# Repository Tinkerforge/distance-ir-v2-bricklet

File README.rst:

Distance IR Bricklet 2.0
========================

This repository contains the firmware source code and the hardware design
files. The documentation generator configs can be found at
https://github.com/Tinkerforge/generators

Repository Content
------------------

software/:
 * examples/: Examples for all supported languages
 * build/: Compiled files
 * src/: Source code of firmware
 * Makefile: Makefile to build project

hardware/:
 * Contains KiCad project files and additionally schematics as PDF

datasheets/:
 * Contains datasheets for sensors and complex ICs that are used

Hardware
--------

The hardware is designed with the open source EDA Suite KiCad
(http://www.kicad.org). Before you are able to open the files,
you have to install the Tinkerforge kicad-libraries
(https://github.com/Tinkerforge/kicad-libraries). You can either clone
them directly in hardware/ or clone them in a separate folder and
symlink them into hardware/
(ln -s kicad_path/kicad-libraries project_path/hardware). After that you
can open the .pro file in hardware/ with KiCad and from there view and
modify the schematics and the PCB layout.

Software
--------

If you want to do your own Brick/Bricklet firmware development we highly
recommend that you use our build environment setup script and read the
tutorial (https://www.tinkerforge.com/en/doc/Tutorials/Tutorial_Build_Environment/Tutorial.html).

To compile the C code we recommend you to install the newest GNU Arm Embedded
Toolchain (https://launchpad.net/gcc-arm-embedded/+download).
You also need to install bricklib2 (https://github.com/Tinkerforge/bricklib2).

You can either clone it directly in software/src/ or clone it in a
separate folder and symlink it into software/src/
(ln -s bricklib_path/bricklib2 project_path/software/src/). Finally make sure to
have CMake installed (http://www.cmake.org/cmake/resources/software.html).

After that you can build the firmware by invoking make in software/.
The firmware (.zbin) can then be found in software/build/ and uploaded
with brickv (click button "Flashing" on start screen).

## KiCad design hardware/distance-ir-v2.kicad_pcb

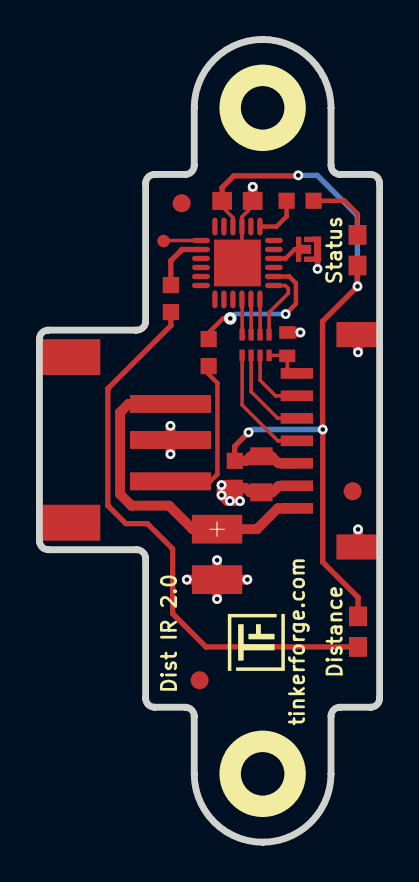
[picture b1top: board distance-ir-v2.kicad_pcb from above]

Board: 2 copper layers, 18.9 x 44.6 mm, 24 parts (2 on the bottom side), 19 nets.

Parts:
C1: 100nF; C0603E
C2: 100µF/10V; 3528-21
C3: 220pF; C0402E
C4: 10uF; C0805
C5: 1uF; C0603F
D1: blue; D0603E
D2: green; D0603E
Fiducial_Mark: VAL**; Fiducial_Mark
Fiducial_Mark#2, Fiducial_Mark#3: VAL**; Fiducial_Mark
P1: CON-SENSOR2
P2: DEBUG; DEBUG_PAD
P3: BOOT; SolderJumper
P4: S3B-PH-SM4
R2, R3, R4: 1k; R0603F
RP1: 82; 4X0402
Ref**: Val**; Logo_31x31
U2, U3: DRILL; DRILL_NP
U4: XMC1302; QFN24-4x4mm-0.5mm
VAL: WEEE_7mm
VAL#2: CE_5mm

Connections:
+5V: C2.1, P1.1, P4.1
GND: C1.2, C2.2, C3.2, C4.2, C5.2, P1.2, P1.EP, P3.1, P4.2, U4.9, U4.EXP
IN_1: R2.2, U4.2
unnamed: C3.1, P1.7, RP1.4
unnamed: D1.2, R3.2
unnamed: D2.2, R4.2
unnamed: P1.4, RP1.1
unnamed: P1.5, RP1.2
unnamed: P1.6, RP1.3
unnamed: P2.1, U4.13
unnamed: P3.2, U4.4
unnamed: P4.3, R2.1
unnamed: R3.1, U4.7
unnamed: R4.1, U4.14
S-CLK: RP1.7, U4.23
S-CS: RP1.8, U4.22
S-MISO: RP1.5, U4.1
S-MOSI: RP1.6, U4.24
VCC: C1.1, C4.1, C5.1, D1.1, D2.1, P1.3, U4.10

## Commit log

2018-05-14 Add datasheets
2018-05-14 Add errata
2018-05-14 Add schematic
2018-05-14 Add layout
2018-05-15 Add .gitignore
2018-06-07 improve routing, add distance led
2018-06-28 Fix readme
2018-07-11 fix origin
2018-07-17 specify processor
2018-07-17 Add auto-generated firmware stub
2018-07-25 Update datasheet
2018-07-26 Remove obsolete datasheet (GP2D120 sensor is EOL)
2018-07-26 Implement Distance IR Bricklet 2.0 firmware and API
2018-07-26 Add calibration data and lookup table script
2018-07-26 Make sure lookup tables are constants
    So GCC can put them in flash instead of RAM.
2018-07-26 Turn debug off
2018-07-31 Add 3d model (*.FCStd & *.step)
2018-07-31 Add PDF schematic
2018-09-07 Add examples
2018-10-02 Add BOOTLOADER_FIX_POINTER_END define
2018-10-04 Fix moving-average-length API type
2018-10-04 Add rev to changelog
2018-10-16 Remove in-development marker
2018-11-06 Add rust examples
2018-11-07 rust: Accept host names for ip connection, fix naming inconsistencies
2018-11-07 rust: Rename callback receivers.
2018-12-14 Add go examples.
2018-12-14 go: Fix printf parameters.
2018-12-18 go: Change import path.
2018-12-18 go: Change import path again.
2018-12-19 Make lookup table script Python3 compatible
2018-12-19 Make configuration of script easier to understand
2018-12-20 Use constant
2018-12-20 Use DISTANCE_SENSOR_NUM constant
    This way the check always stays up-to-date, even if a new lookup-table
    is added
2018-12-20 rust: Reformat examples.
2019-01-24 mqtt: Add examples.
2019-01-24 mqtt: Fix example header.
2019-01-24 mqtt: Remove executable bit in example permissions.
2019-01-24 go: Minor example fixes.
2019-01-24 mqtt: Minor example fixes.
2019-03-28 mqtt: Fix whitespace.
2019-05-29 Set LED config
2019-05-29 Increase version for new release (changes in bricklib2)
2019-08-22 c: Adapt to bindings changes
2020-01-13 examples: Use python3 input instead of python2 raw_input.
2020-01-13 examples: mqtt: Remove trailing whitespace.
2020-03-11 changed board outline, added rounded corners, updated boot pad footprint
2020-08-19 Add uc examples.
2020-08-25 uc: Fix whitespace
2020-08-27 uc: Fix warnings.
2020-09-02 uc: Add example driver note.
2020-10-16 uc: Fix divisor type.
2021-10-25 Update KiCad link
    https://www.kicad.org/blog/2021/10/Avoid-links-to-former-kicad-domain/
2022-04-19 examples: uc: Rename TF_HalContext to TF_HAL.
2022-04-27 uc: Adapt to bindings changes
2022-07-06 Add license files.
2025-10-04 Fix compatibility with new Docker build image (GCC 14.2.1)
2026-05-20 update to new kicad version

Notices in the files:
hardware/distance-ir-v2.kicad_pcb:
Licensed under CERN OHL v.1.1
Copyright (©) 2018, L.Lauer
Copyright Tinkerforge GmbH 2018.
This documentation describes Open Hardware and is licensed under the
CERN OHL v. 1.1.
